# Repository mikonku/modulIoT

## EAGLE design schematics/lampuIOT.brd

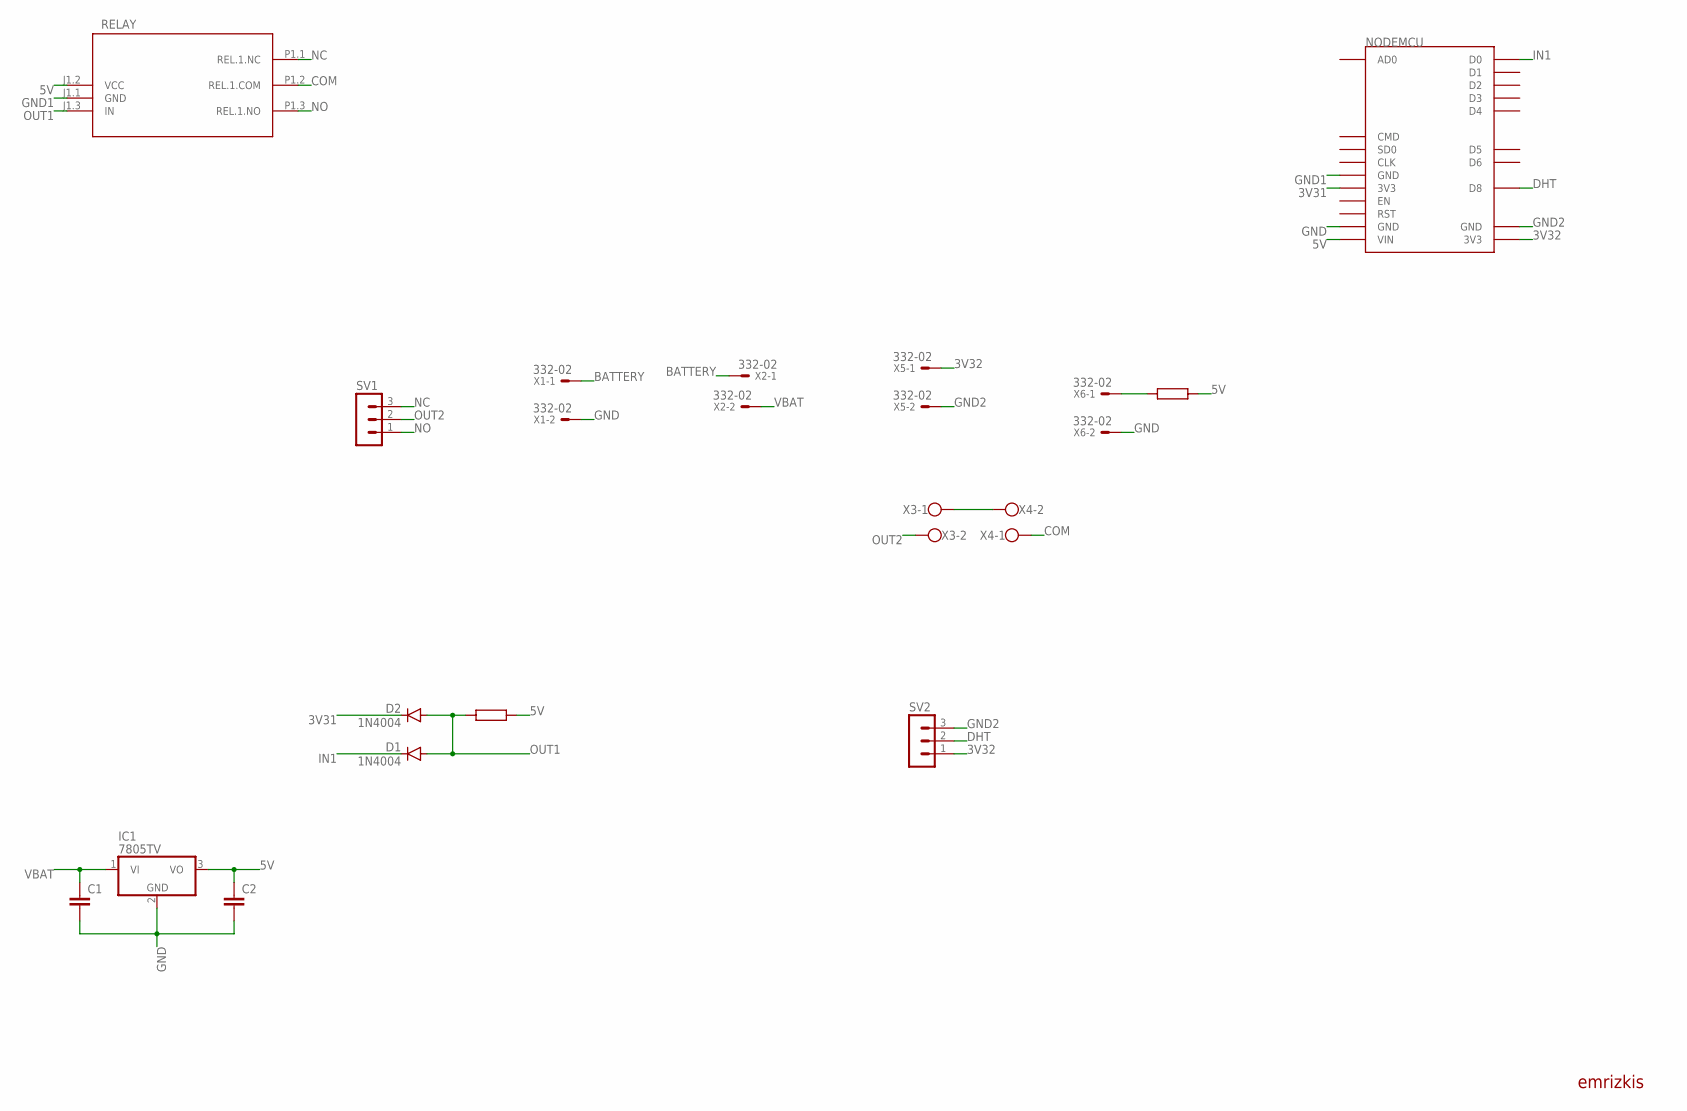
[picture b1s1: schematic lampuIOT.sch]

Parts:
C1, C2: C2.5/2; C2.5-2
D1, D2: 1N4004; DO41-10
IC1: 7805TV; TO220V
NODEMCU: ESP12E_DEVKIT
R, R1: RESISTOR
RELAY: RELAY1CH
SV1, SV2: MA03-1
X1, X2, X5, X6: 332-02
X3, X4: W237-102

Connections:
3V31: D2.C, NODEMCU.3V3@0 (3V3); also elsewhere on the board
3V32: NODEMCU.3V3@2 (3V3), SV2.1, X5.1; also elsewhere on the board
5V: C2.1, IC1.3 (VO), NODEMCU.VIN, R.P$1 (1), R1.P$1 (1), RELAY.J1.2 (VCC); also elsewhere on the board
BATTERY: X1.1, X2.1
COM: RELAY.P1.2 (REL.1.COM), X4.1
DHT: NODEMCU.D8, SV2.2; also elsewhere on the board
GND: C1.2, C2.2, IC1.2 (GND), NODEMCU.GND@1 (GND), X1.2, X6.2; also elsewhere on the board
GND1: NODEMCU.GND@0 (GND), RELAY.J1.1 (GND); also elsewhere on the board
GND2: NODEMCU.GND@3 (GND), SV2.3, X5.2; also elsewhere on the board
IN1: D1.C, NODEMCU.D0; also elsewhere on the board
unnamed: X3.1, X4.2
unnamed: R1.P$2 (2), X6.1
NC: RELAY.P1.1 (REL.1.NC), SV1.3
NO: RELAY.P1.3 (REL.1.NO), SV1.1
OUT1: D1.A, D2.A, R.P$2 (2), RELAY.J1.3 (IN)
OUT2: SV1.2, X3.2
VBAT: C1.1, IC1.1 (VI), X2.2

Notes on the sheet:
emrizkis

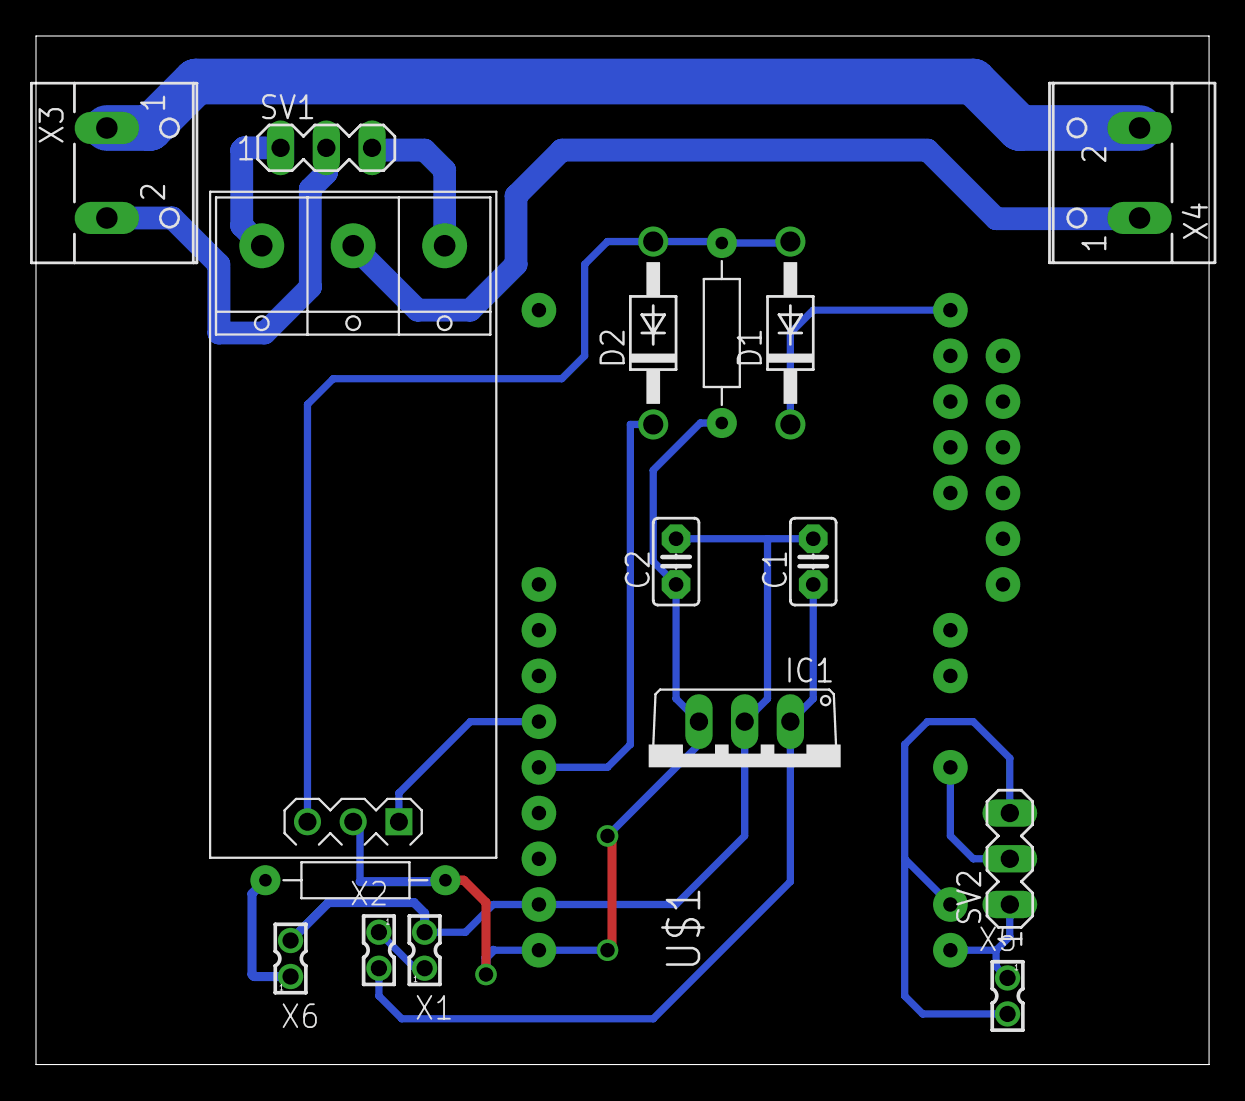
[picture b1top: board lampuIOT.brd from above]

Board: 2 copper layers, 65.2 x 57.1 mm, 17 parts (0 on the bottom side), 17 nets.

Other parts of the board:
U$1: ESP12E_DEVKIT

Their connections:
3V31: U$1.3V3@0; also elsewhere on the board
3V32: U$1.3V3@2; also elsewhere on the board
5V: U$1.VIN; also elsewhere on the board
DHT: U$1.D8; also elsewhere on the board
GND: U$1.GND@1; also elsewhere on the board
GND1: U$1.GND@0; also elsewhere on the board
GND2: U$1.GND@3; also elsewhere on the board
IN1: U$1.D0; also elsewhere on the board

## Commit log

2020-12-30 add schema and example code

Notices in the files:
parts and their libraries:
nodemcu_lolin: Released under the Creative Commons Attribution 4.0 International License: http://creativecommons.org/licenses/by/4.0
